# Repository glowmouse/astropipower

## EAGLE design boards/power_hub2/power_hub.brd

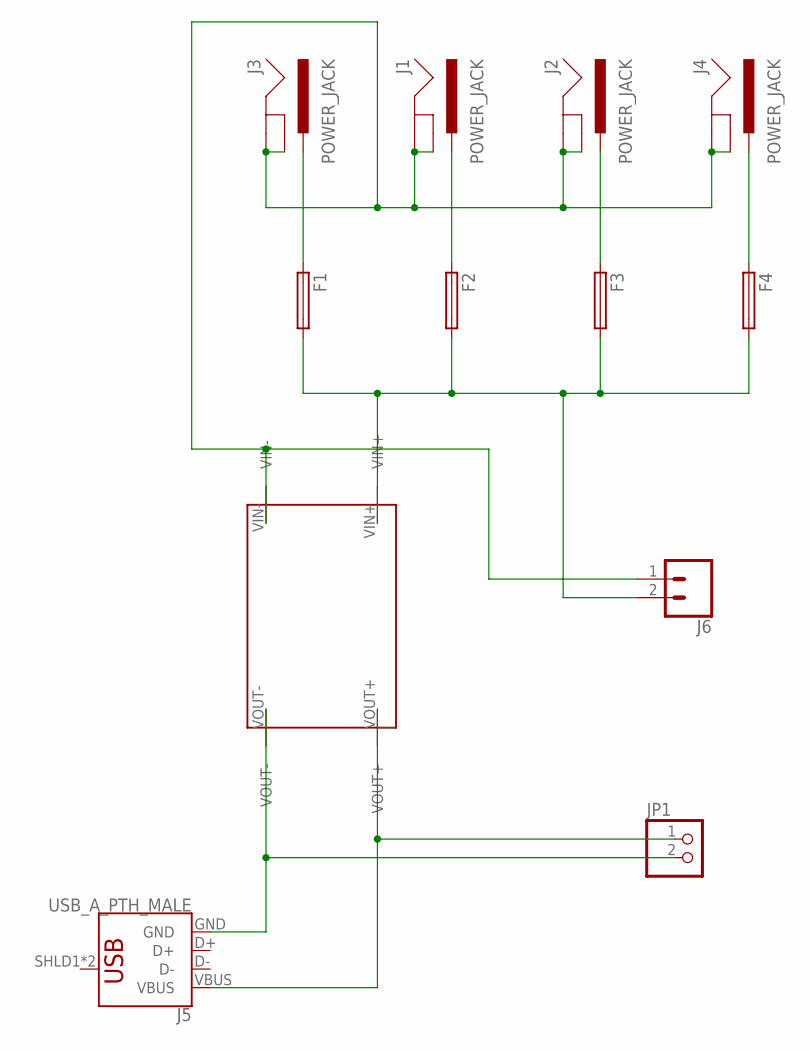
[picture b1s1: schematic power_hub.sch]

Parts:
F1, F2, F3, F4: GSH15
J1, J2, J3, J4: POWER_JACK; POWER_JACK_PTH
J5: USB_A_PTH_MALE; USB-A-H
J6: CONN_023.5MM; SCREWTERMINAL-3.5MM-2
JP1: PINHD-1X2; 1X02
U$1: DCPOWERCONV_PHUB

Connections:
unnamed: F1.1, J3.PWR
unnamed: F2.1, J1.PWR
unnamed: F3.1, J2.PWR
unnamed: J5.VBUS, JP1.1, U$1.VOUT+
unnamed: F1.2, F2.2, F3.2, F4.2, J6.2, U$1.VIN+
unnamed: F4.1, J4.PWR
unnamed: J5.GND, JP1.2, U$1.VOUT-
unnamed: J1.GND, J1.GNDBREAK, J2.GND, J2.GNDBREAK, J3.GND, J3.GNDBREAK, J4.GND, J4.GNDBREAK, J6.1, U$1.VIN-

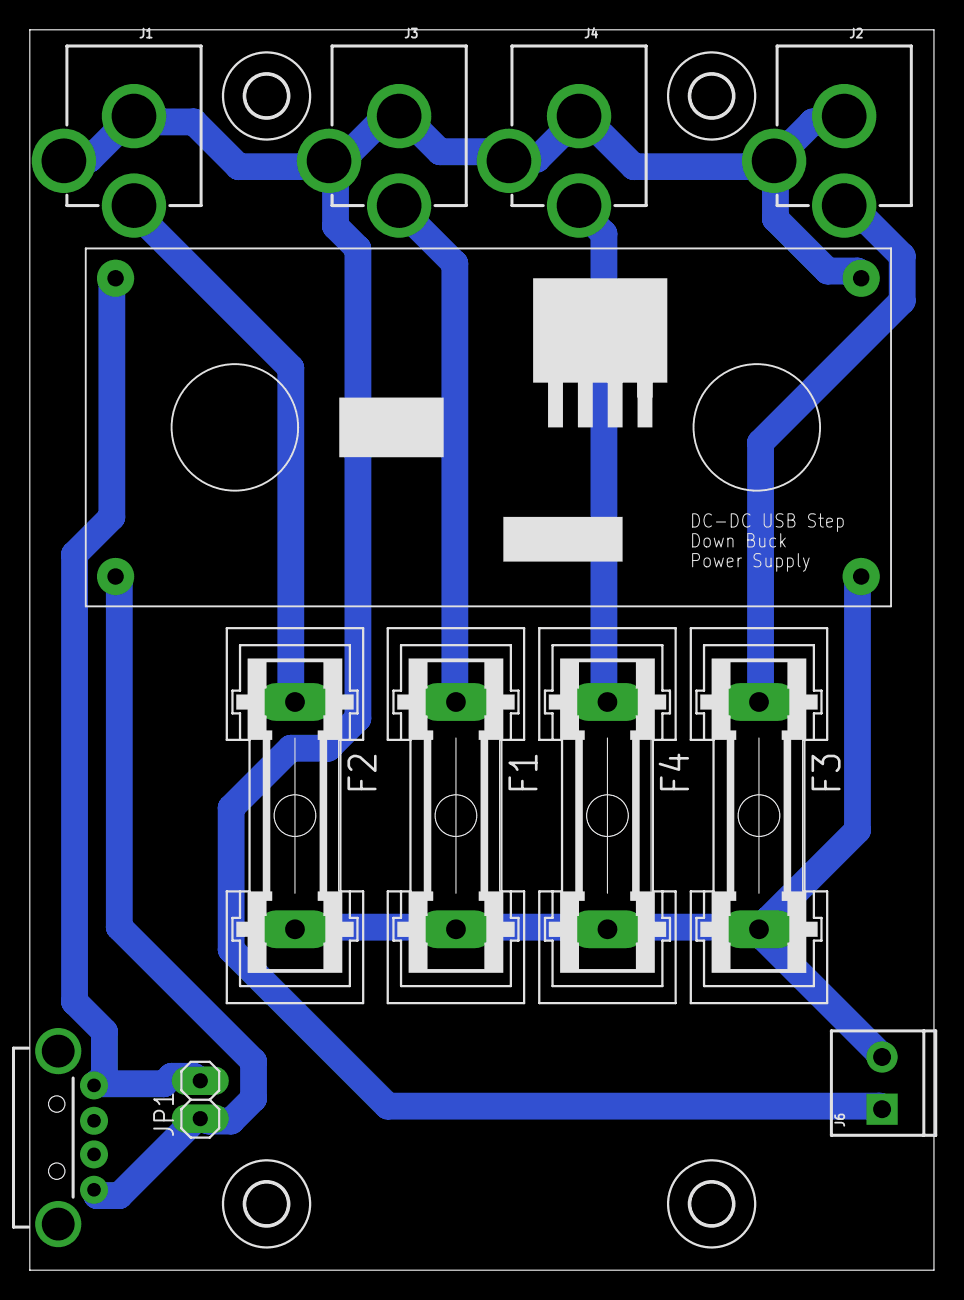
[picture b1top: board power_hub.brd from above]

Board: 2 copper layers, 60.6 x 83.2 mm, 16 parts (0 on the bottom side), 8 nets.

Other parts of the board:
U$2, U$3, U$4, U$5: 2,8

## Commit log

2019-01-21 Power hub board for Raspberry Pi.

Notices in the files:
parts and their libraries:
SparkFun-Connectors: Licensing: Creative Commons ShareAlike 4.0 International - https://creativecommons.org/licenses/by-sa/4.0
